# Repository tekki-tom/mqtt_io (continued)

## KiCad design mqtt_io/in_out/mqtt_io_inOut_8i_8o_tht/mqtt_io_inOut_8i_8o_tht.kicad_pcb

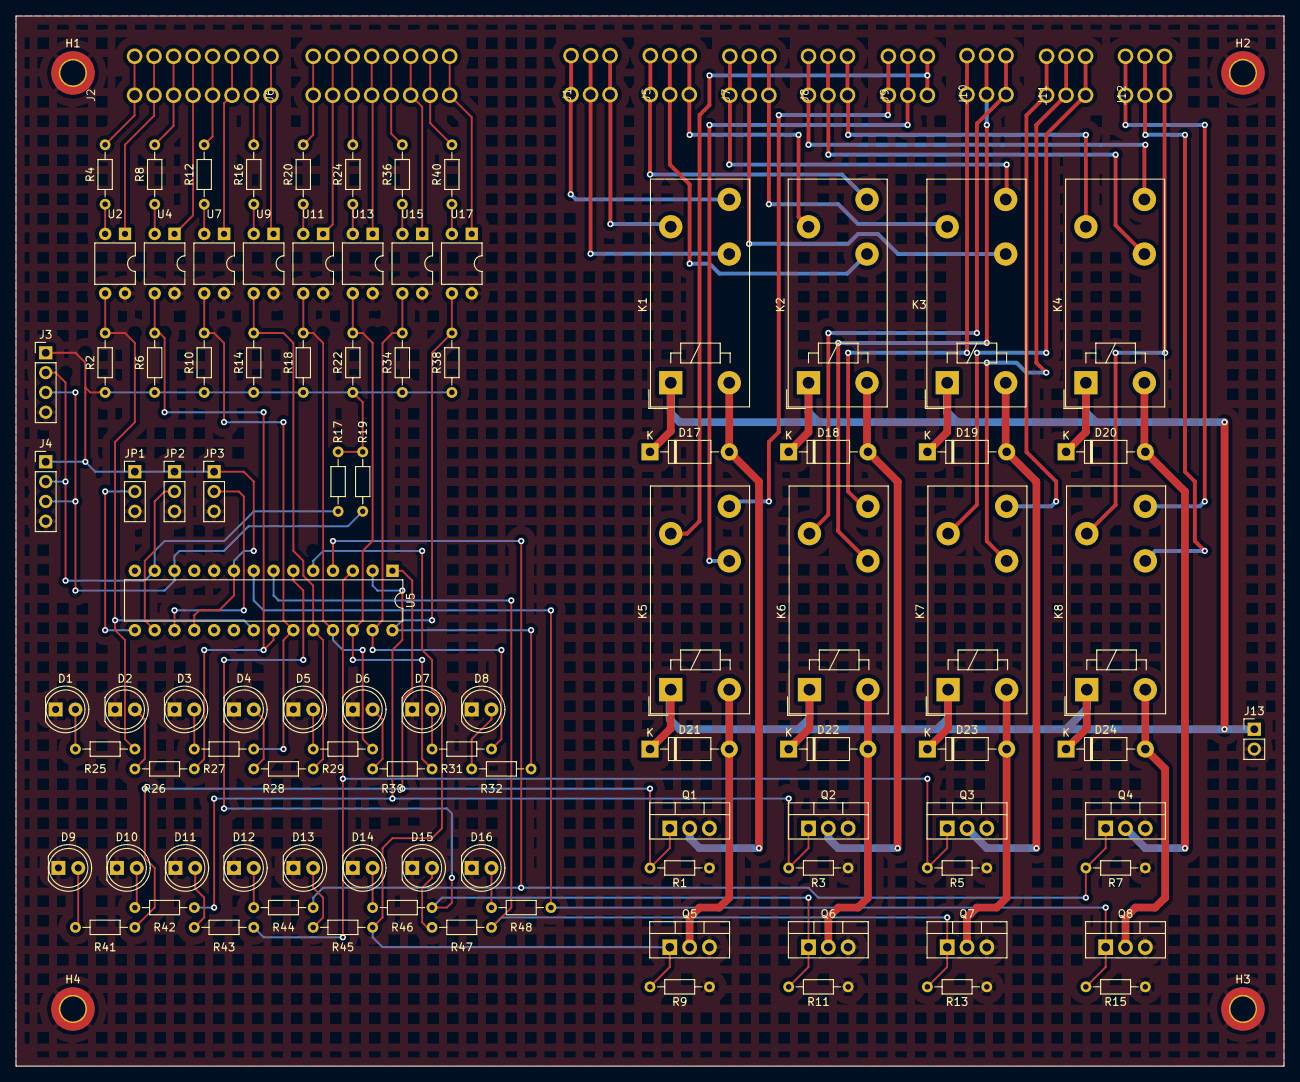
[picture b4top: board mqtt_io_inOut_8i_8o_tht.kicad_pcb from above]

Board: 2 copper layers, 162.6 x 134.6 mm, 111 parts (0 on the bottom side), 96 nets.

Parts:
D1, D2, D3, D4, D5, D6, D7, D8, D9, D10, D11, D12, D13, D14, D15, D16: LED; LED_D5.0mm
D17, D18, D19, D20, D21, D22, D23, D24: 1N4001; D_DO-41_SOD81_P10.16mm_Horizontal
H1, H2, H3, H4: MountingHole_Pad; MountingHole_3.2mm_M3_DIN965_Pad_TopBottom
J1, J5, J7, J8, J9, J10, J11, J12: AST_041-3
J2, J6: AST041-08
J3, J4: Conn_01x04_Pin; PinHeader_1x04_P2.54mm_Vertical
J13: Conn_01x02; PinHeader_1x02_P2.54mm_Vertical
JP1, JP2, JP3: Jumper_3_Open; PinHeader_1x03_P2.54mm_Vertical
K1, K2, K3, K4, K5, K6, K7, K8: FINDER-40.31; Relay_SPDT_Finder_40.31
Q1, Q2, Q3, Q4, Q5, Q6, Q7, Q8: IRFZ24N; TO-220-3_Vertical
R1, R3, R5, R7, R9, R11, R13, R15: 100kR; R_Axial_DIN0204_L3.6mm_D1.6mm_P7.62mm_Horizontal
R2, R6, R10, R14, R18, R22, R34, R38: 10kR; R_Axial_DIN0204_L3.6mm_D1.6mm_P7.62mm_Horizontal
R4, R8, R12, R16, R20, R24, R36, R40: 1200R; R_Axial_DIN0204_L3.6mm_D1.6mm_P7.62mm_Horizontal
R17, R19: 4k7; R_Axial_DIN0204_L3.6mm_D1.6mm_P7.62mm_Horizontal
R25, R26, R27, R28, R29, R30, R31, R32, R41, R42, R43, R44, R45, R46, R47, R48: 330R; R_Axial_DIN0204_L3.6mm_D1.6mm_P7.62mm_Horizontal
U2, U4, U7, U9, U11, U13, U15, U17: LTV-817; DIP-4_W7.62mm
U5: MCP23017_SP; DIP-28_W7.62mm

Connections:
/AD0: JP1.2 (C), U5.15 (A0)
/AD1: JP2.2 (C), U5.16 (A1)
/AD2: JP3.2 (C), U5.17 (A2)
/a0: R2.2, R25.2, U2.3, U5.21 (GPA0)
/a1: R6.2, R26.2, U4.3, U5.22 (GPA1)
/a2: R10.2, R27.2, U5.23 (GPA2), U7.3
/a3: R14.2, R28.2, U5.24 (GPA3), U9.3
/a4: R18.2, R29.2, U5.25 (GPA4), U11.3
/a5: R22.2, R30.2, U5.26 (GPA5), U13.3
/a6: R31.2, R34.2, U5.27 (GPA6), U15.3
/a7: R32.2, R38.2, U5.28 (GPA7), U17.3
/b0: Q1.1 (G), R1.2, R41.2, U5.1 (GPB0)
/b1: Q2.1 (G), R3.2, R42.2, U5.2 (GPB1)
/b2: Q3.1 (G), R5.2, R43.2, U5.3 (GPB2)
/b3: Q4.1 (G), R7.2, R44.2, U5.4 (GPB3)
/b4: Q5.1 (G), R9.2, R45.2, U5.5 (GPB4)
/b5: Q6.1 (G), R11.2, R46.2, U5.6 (GPB5)
/b6: Q7.1 (G), R13.2, R47.2, U5.7 (GPB6)
/b7: Q8.1 (G), R15.2, R48.2, U5.8 (GPB7)
GND: D1.1 (K), D2.1 (K), D3.1 (K), D4.1 (K), D5.1 (K), D6.1 (K), D7.1 (K), D8.1 (K), D9.1 (K), D10.1 (K), D11.1 (K), D12.1 (K), D13.1 (K), D14.1 (K), D15.1 (K), D16.1 (K), H1.1, H2.1, H3.1, H4.1, J3.4, J4.4, J13.2, JP1.3 (B), JP2.3 (B), JP3.3 (B), Q1.3 (S), Q2.3 (S), Q3.3 (S), Q4.3 (S), Q5.3 (S), Q6.3 (S), Q7.3 (S), Q8.3 (S), R1.1, R3.1, R5.1, R7.1, R9.1, R11.1, R13.1, R15.1, U2.4, U4.4, U5.10 (VSS), U7.4, U9.4, U11.4, U13.4, U15.4, U17.4
unnamed: D1.2 (A), R25.1
unnamed: D2.2 (A), R26.1
unnamed: D3.2 (A), R27.1
unnamed: D4.2 (A), R28.1
unnamed: D5.2 (A), R29.1
unnamed: D6.2 (A), R30.1
unnamed: D7.2 (A), R31.1
unnamed: D8.2 (A), R32.1
unnamed: D9.2 (A), R41.1
unnamed: D10.2 (A), R42.1
unnamed: D11.2 (A), R43.1
unnamed: D12.2 (A), R44.1
unnamed: D13.2 (A), R45.1
unnamed: D14.2 (A), R46.1
unnamed: D15.2 (A), R47.1
unnamed: D16.2 (A), R48.1
unnamed: D17.2 (A), K1.A2, Q1.2 (D)
unnamed: D18.2 (A), K2.A2, Q2.2 (D)
unnamed: D19.2 (A), K3.A2, Q3.2 (D)
unnamed: D20.2 (A), K4.A2, Q4.2 (D)
unnamed: D21.2 (A), K5.A2, Q5.2 (D)
unnamed: D22.2 (A), K6.A2, Q6.2 (D)
unnamed: D23.2 (A), K7.A2, Q7.2 (D)
unnamed: D24.2 (A), K8.A2, Q8.2 (D)
unnamed: J1.1, K1.14
unnamed: J1.2, K1.12
unnamed: J1.3, K1.11
unnamed: J2.1 (io), R4.2
unnamed: J2.2 (io), U2.1
unnamed: J2.3 (io), R8.2
unnamed: J2.4 (io), U4.1
unnamed: J2.5 (io), R12.2
unnamed: J2.6 (io), U7.1
unnamed: J2.7 (io), R16.2
unnamed: J2.8 (io), U9.1
unnamed: J3.2, J4.2, R17.1, U5.13 (SDA)
unnamed: J3.3, J4.3, R19.1, U5.12 (SCK)
unnamed: J5.1, K2.14
unnamed: J5.2, K2.12
unnamed: J5.3, K2.11
unnamed: J6.1 (io), R20.2
unnamed: J6.2 (io), U11.1
unnamed: J6.3 (io), R24.2
unnamed: J6.4 (io), U13.1
unnamed: J6.5 (io), R36.2
unnamed: J6.6 (io), U15.1
unnamed: J6.7 (io), R40.2
unnamed: J6.8 (io), U17.1
unnamed: J7.1, K3.14
unnamed: J7.2, K3.12
unnamed: J7.3, K3.11
unnamed: J8.1, K4.14
unnamed: J8.2, K4.12
unnamed: J8.3, K4.11
unnamed: J9.1, K5.14
unnamed: J9.2, K5.12
unnamed: J9.3, K5.11
unnamed: J10.1, K6.14
unnamed: J10.2, K6.12
unnamed: J10.3, K6.11
unnamed: J11.1, K7.14
unnamed: J11.2, K7.12
unnamed: J11.3, K7.11
unnamed: J12.1, K8.14
unnamed: J12.2, K8.12
unnamed: J12.3, K8.11
unnamed: R4.1, U2.2
unnamed: R8.1, U4.2
unnamed: R12.1, U7.2
unnamed: R16.1, U9.2
unnamed: R20.1, U11.2
unnamed: R24.1, U13.2
unnamed: R36.1, U15.2
unnamed: R40.1, U17.2
VCC: D17.1 (K), D18.1 (K), D19.1 (K), D20.1 (K), D21.1 (K), D22.1 (K), D23.1 (K), D24.1 (K), J13.1, K1.A1, K2.A1, K3.A1, K4.A1, K5.A1, K6.A1, K7.A1, K8.A1
VDD: J3.1, J4.1, JP1.1 (A), JP2.1 (A), JP3.1 (A), R2.1, R6.1, R10.1, R14.1, R17.2, R18.1, R19.2, R22.1, R34.1, R38.1, U5.9 (VDD), U5.18 (~RESET)

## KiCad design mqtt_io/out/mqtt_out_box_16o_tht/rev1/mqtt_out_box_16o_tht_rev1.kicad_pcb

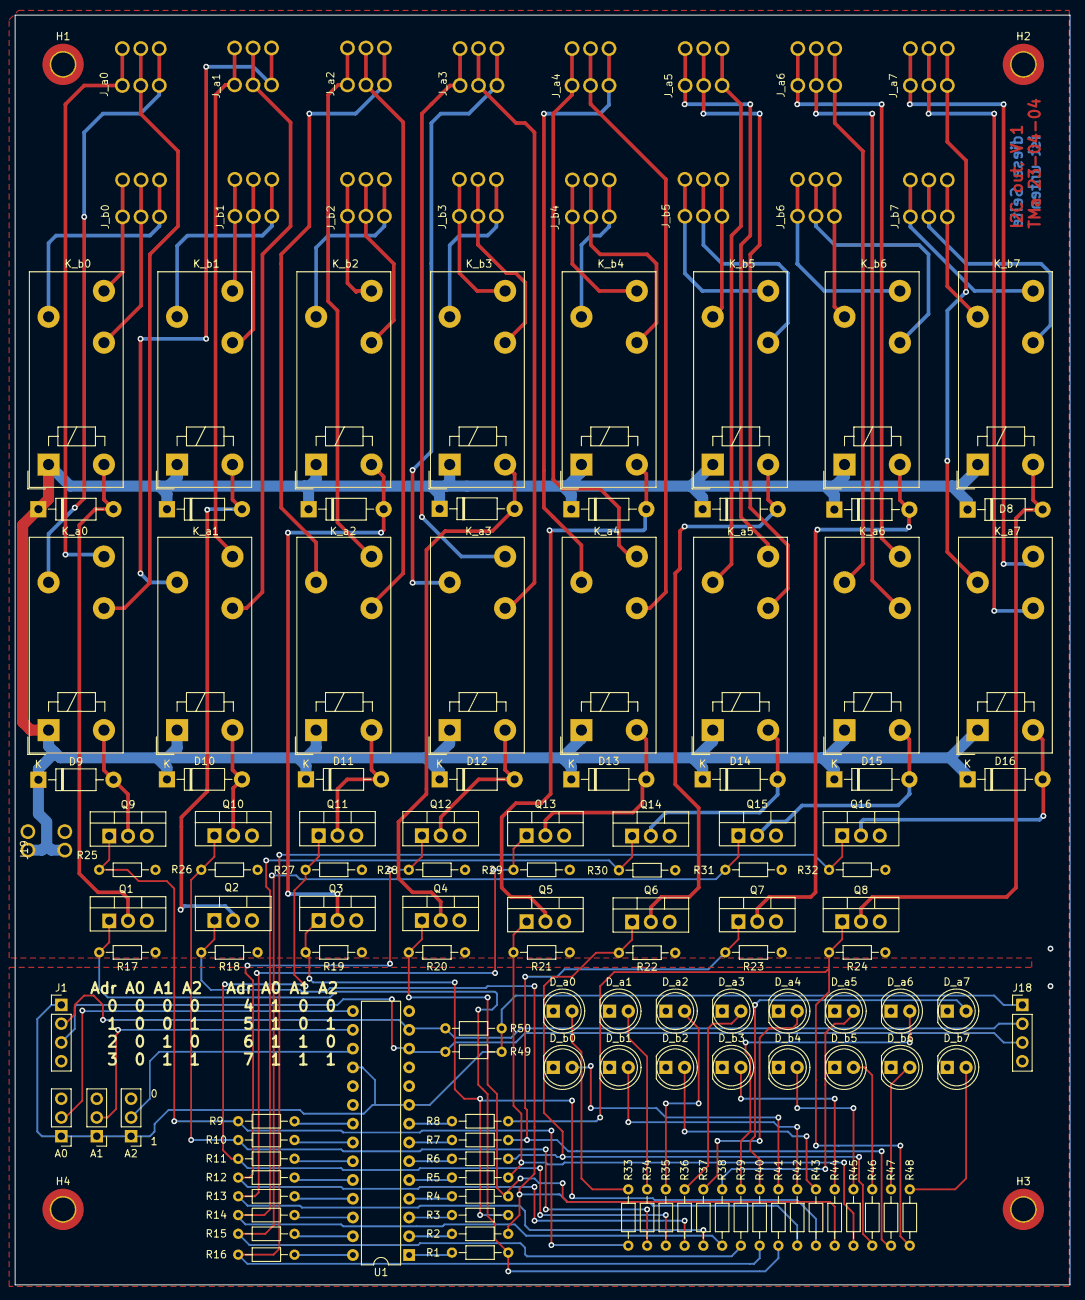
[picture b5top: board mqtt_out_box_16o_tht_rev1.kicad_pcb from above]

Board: 2 copper layers, 142.8 x 171.9 mm, 141 parts (0 on the bottom side), 120 nets.

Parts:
A0, A1, A2: Jumper_3_Open; PinHeader_1x03_P2.54mm_Vertical
D1, D2, D3, D4, D5, D6, D7, D8, D9, D10, D11, D12, D13, D14, D15, D16: 1N4001; D_DO-41_SOD81_P10.16mm_Horizontal
D_a0, D_a1, D_a2, D_a3, D_a4, D_a5, D_a6, D_a7: LED; LED_D5.0mm
D_b0, D_b1, D_b2, D_b3, D_b4, D_b5, D_b6, D_b7: LED; LED_D5.0mm
H1, H2, H3, H4: MountingHole_Pad; MountingHole_3.2mm_M3_DIN965_Pad_TopBottom
J1, J18: Conn_01x04_Pin; PinHeader_1x04_P2.54mm_Vertical
J19: AST_041-2
J_a0, J_a1, J_a2, J_a3, J_a4, J_a5, J_a6, J_a7: AST_041-3
J_b0, J_b1, J_b2, J_b3, J_b4, J_b5, J_b6, J_b7: AST_041-3
K_a0, K_a1, K_a2, K_a3, K_a4, K_a5, K_a6, K_a7: FINDER-40.31; Relay_SPDT_Finder_40.31
K_b0, K_b1, K_b2, K_b3, K_b4, K_b5, K_b6, K_b7: FINDER-40.31; Relay_SPDT_Finder_40.31
Q1, Q2, Q3, Q4, Q5, Q6, Q7, Q8, Q9, Q10, Q11, Q12, Q13, Q14, Q15, Q16: IRFZ24N; TO-220-3_Vertical
R1, R2, R3, R4, R5, R6, R7, R8, R9, R10, R11, R12, R13, R14, R15, R16: 100R; R_Axial_DIN0204_L3.6mm_D1.6mm_P7.62mm_Horizontal
R17, R18, R19, R20, R21, R22, R23, R24, R25, R26, R27, R28, R29, R30, R31, R32: 100kR; R_Axial_DIN0204_L3.6mm_D1.6mm_P7.62mm_Horizontal
R33, R34, R35, R36, R37, R38, R39, R40, R41, R42, R43, R44, R45, R46, R47, R48: 330R; R_Axial_DIN0204_L3.6mm_D1.6mm_P7.62mm_Horizontal
R49, R50: 4k7; R_Axial_DIN0204_L3.6mm_D1.6mm_P7.62mm_Horizontal
U1: MCP23017_SP; DIP-28_W7.62mm

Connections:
/AD0: A0.2 (C), U1.15 (A0)
/AD1: A1.2 (C), U1.16 (A1)
/AD2: A2.2 (C), U1.17 (A2)
/a0: Q9.1 (G), R9.2, R25.2, R33.2
/a1: Q10.1 (G), R10.2, R26.2, R34.2
/a2: Q11.1 (G), R11.2, R27.2, R35.2
/a3: Q12.1 (G), R12.2, R28.2, R36.2
/a4: Q13.1 (G), R13.2, R29.2, R37.2
/a5: Q14.1 (G), R14.2, R30.2, R38.2
/a6: Q15.1 (G), R15.2, R31.2, R39.2
/a7: Q16.1 (G), R16.2, R32.2, R40.2
/b0: Q1.1 (G), R1.2, R17.2, R41.2
/b1: Q2.1 (G), R2.2, R18.2, R42.2
/b2: Q3.1 (G), R3.2, R19.2, R43.2
/b3: Q4.1 (G), R4.2, R20.2, R44.2
/b4: Q5.1 (G), R5.2, R21.2, R45.2
/b5: Q6.1 (G), R6.2, R22.2, R46.2
/b6: Q7.1 (G), R7.2, R23.2, R47.2
/b7: Q8.1 (G), R8.2, R24.2, R48.2
GND: A0.3 (B), A1.3 (B), A2.3 (B), D_a0.1 (K), D_a1.1 (K), D_a2.1 (K), D_a3.1 (K), D_a4.1 (K), D_a5.1 (K), D_a6.1 (K), D_a7.1 (K), D_b0.1 (K), D_b1.1 (K), D_b2.1 (K), D_b3.1 (K), D_b4.1 (K), D_b5.1 (K), D_b6.1 (K), D_b7.1 (K), H1.1, H2.1, H3.1, H4.1, J1.4, J18.4, J19.2, Q1.3 (S), Q2.3 (S), Q3.3 (S), Q4.3 (S), Q5.3 (S), Q6.3 (S), Q7.3 (S), Q8.3 (S), Q9.3 (S), Q10.3 (S), Q11.3 (S), Q12.3 (S), Q13.3 (S), Q14.3 (S), Q15.3 (S), Q16.3 (S), R17.1, R18.1, R19.1, R20.1, R21.1, R22.1, R23.1, R24.1, R25.1, R26.1, R27.1, R28.1, R29.1, R30.1, R31.1, R32.1, U1.10 (VSS)
unnamed: D1.2 (A), K_b0.A2, Q1.2 (D)
unnamed: D2.2 (A), K_b1.A2, Q2.2 (D)
unnamed: D3.2 (A), K_b2.A2, Q3.2 (D)
unnamed: D4.2 (A), K_b3.A2, Q4.2 (D)
unnamed: D5.2 (A), K_b4.A2, Q5.2 (D)
unnamed: D6.2 (A), K_b5.A2, Q6.2 (D)
unnamed: D7.2 (A), K_b6.A2, Q7.2 (D)
unnamed: D8.2 (A), K_b7.A2, Q8.2 (D)
unnamed: D9.2 (A), K_a0.A2, Q9.2 (D)
unnamed: D10.2 (A), K_a1.A2, Q10.2 (D)
unnamed: D11.2 (A), K_a2.A2, Q11.2 (D)
unnamed: D12.2 (A), K_a3.A2, Q12.2 (D)
unnamed: D13.2 (A), K_a4.A2, Q13.2 (D)
unnamed: D14.2 (A), K_a5.A2, Q14.2 (D)
unnamed: D15.2 (A), K_a6.A2, Q15.2 (D)
unnamed: D16.2 (A), K_a7.A2, Q16.2 (D)
unnamed: D_a0.2 (A), R33.1
unnamed: D_a1.2 (A), R34.1
unnamed: D_a2.2 (A), R35.1
unnamed: D_a3.2 (A), R36.1
unnamed: D_a4.2 (A), R37.1
unnamed: D_a5.2 (A), R38.1
unnamed: D_a6.2 (A), R39.1
unnamed: D_a7.2 (A), R40.1
unnamed: D_b0.2 (A), R41.1
unnamed: D_b1.2 (A), R42.1
unnamed: D_b2.2 (A), R43.1
unnamed: D_b3.2 (A), R44.1
unnamed: D_b4.2 (A), R45.1
unnamed: D_b5.2 (A), R46.1
unnamed: D_b6.2 (A), R47.1
unnamed: D_b7.2 (A), R48.1
unnamed: J1.2, J18.2, R50.1, U1.13 (SDA)
unnamed: J1.3, J18.3, R49.1, U1.12 (SCK)
unnamed: J_a0.1, K_a0.14
unnamed: J_a0.2, K_a0.12
unnamed: J_a0.3, K_a0.11
unnamed: J_a1.1, K_a1.14
unnamed: J_a1.2, K_a1.12
unnamed: J_a1.3, K_a1.11
unnamed: J_a2.1, K_a2.14
unnamed: J_a2.2, K_a2.12
unnamed: J_a2.3, K_a2.11
unnamed: J_a3.1, K_a3.14
unnamed: J_a3.2, K_a3.12
unnamed: J_a3.3, K_a3.11
unnamed: J_a4.1, K_a4.14
unnamed: J_a4.2, K_a4.12
unnamed: J_a4.3, K_a4.11
unnamed: J_a5.1, K_a5.14
unnamed: J_a5.2, K_a5.12
unnamed: J_a5.3, K_a5.11
unnamed: J_a6.1, K_a6.14
unnamed: J_a6.2, K_a6.12
unnamed: J_a6.3, K_a6.11
unnamed: J_a7.1, K_a7.14
unnamed: J_a7.2, K_a7.12
unnamed: J_a7.3, K_a7.11
unnamed: J_b0.1, K_b0.14
unnamed: J_b0.2, K_b0.12
unnamed: J_b0.3, K_b0.11
unnamed: J_b1.1, K_b1.14
unnamed: J_b1.2, K_b1.12
unnamed: J_b1.3, K_b1.11
unnamed: J_b2.1, K_b2.14
unnamed: J_b2.2, K_b2.12
unnamed: J_b2.3, K_b2.11
unnamed: J_b3.1, K_b3.14
unnamed: J_b3.2, K_b3.12
unnamed: J_b3.3, K_b3.11
unnamed: J_b4.1, K_b4.14
unnamed: J_b4.2, K_b4.12
unnamed: J_b4.3, K_b4.11
unnamed: J_b5.1, K_b5.14
unnamed: J_b5.2, K_b5.12
unnamed: J_b5.3, K_b5.11
unnamed: J_b6.1, K_b6.14
unnamed: J_b6.2, K_b6.12
unnamed: J_b6.3, K_b6.11
unnamed: J_b7.1, K_b7.14
unnamed: J_b7.2, K_b7.12
unnamed: J_b7.3, K_b7.11
unnamed: R9.1, U1.21 (GPA0)
unnamed: R10.1, U1.22 (GPA1)
unnamed: R11.1, U1.23 (GPA2)
unnamed: R12.1, U1.24 (GPA3)
unnamed: R13.1, U1.25 (GPA4)
unnamed: R14.1, U1.26 (GPA5)
unnamed: R15.1, U1.27 (GPA6)
unnamed: R16.1, U1.28 (GPA7)
unnamed: R1.1, U1.1 (GPB0)
unnamed: R2.1, U1.2 (GPB1)
unnamed: R3.1, U1.3 (GPB2)
unnamed: R4.1, U1.4 (GPB3)
unnamed: R5.1, U1.5 (GPB4)
unnamed: R6.1, U1.6 (GPB5)
unnamed: R7.1, U1.7 (GPB6)
unnamed: R8.1, U1.8 (GPB7)
VCC: D1.1 (K), D2.1 (K), D3.1 (K), D4.1 (K), D5.1 (K), D6.1 (K), D7.1 (K), D8.1 (K), D9.1 (K), D10.1 (K), D11.1 (K), D12.1 (K), D13.1 (K), D14.1 (K), D15.1 (K), D16.1 (K), J19.1, K_a0.A1, K_a1.A1, K_a2.A1, K_a3.A1, K_a4.A1, K_a5.A1, K_a6.A1, K_a7.A1, K_b0.A1, K_b1.A1, K_b2.A1, K_b3.A1, K_b4.A1, K_b5.A1, K_b6.A1, K_b7.A1
VDD: A0.1 (A), A1.1 (A), A2.1 (A), J1.1, J18.1, R49.2, R50.2, U1.9 (VDD), U1.18 (~RESET)

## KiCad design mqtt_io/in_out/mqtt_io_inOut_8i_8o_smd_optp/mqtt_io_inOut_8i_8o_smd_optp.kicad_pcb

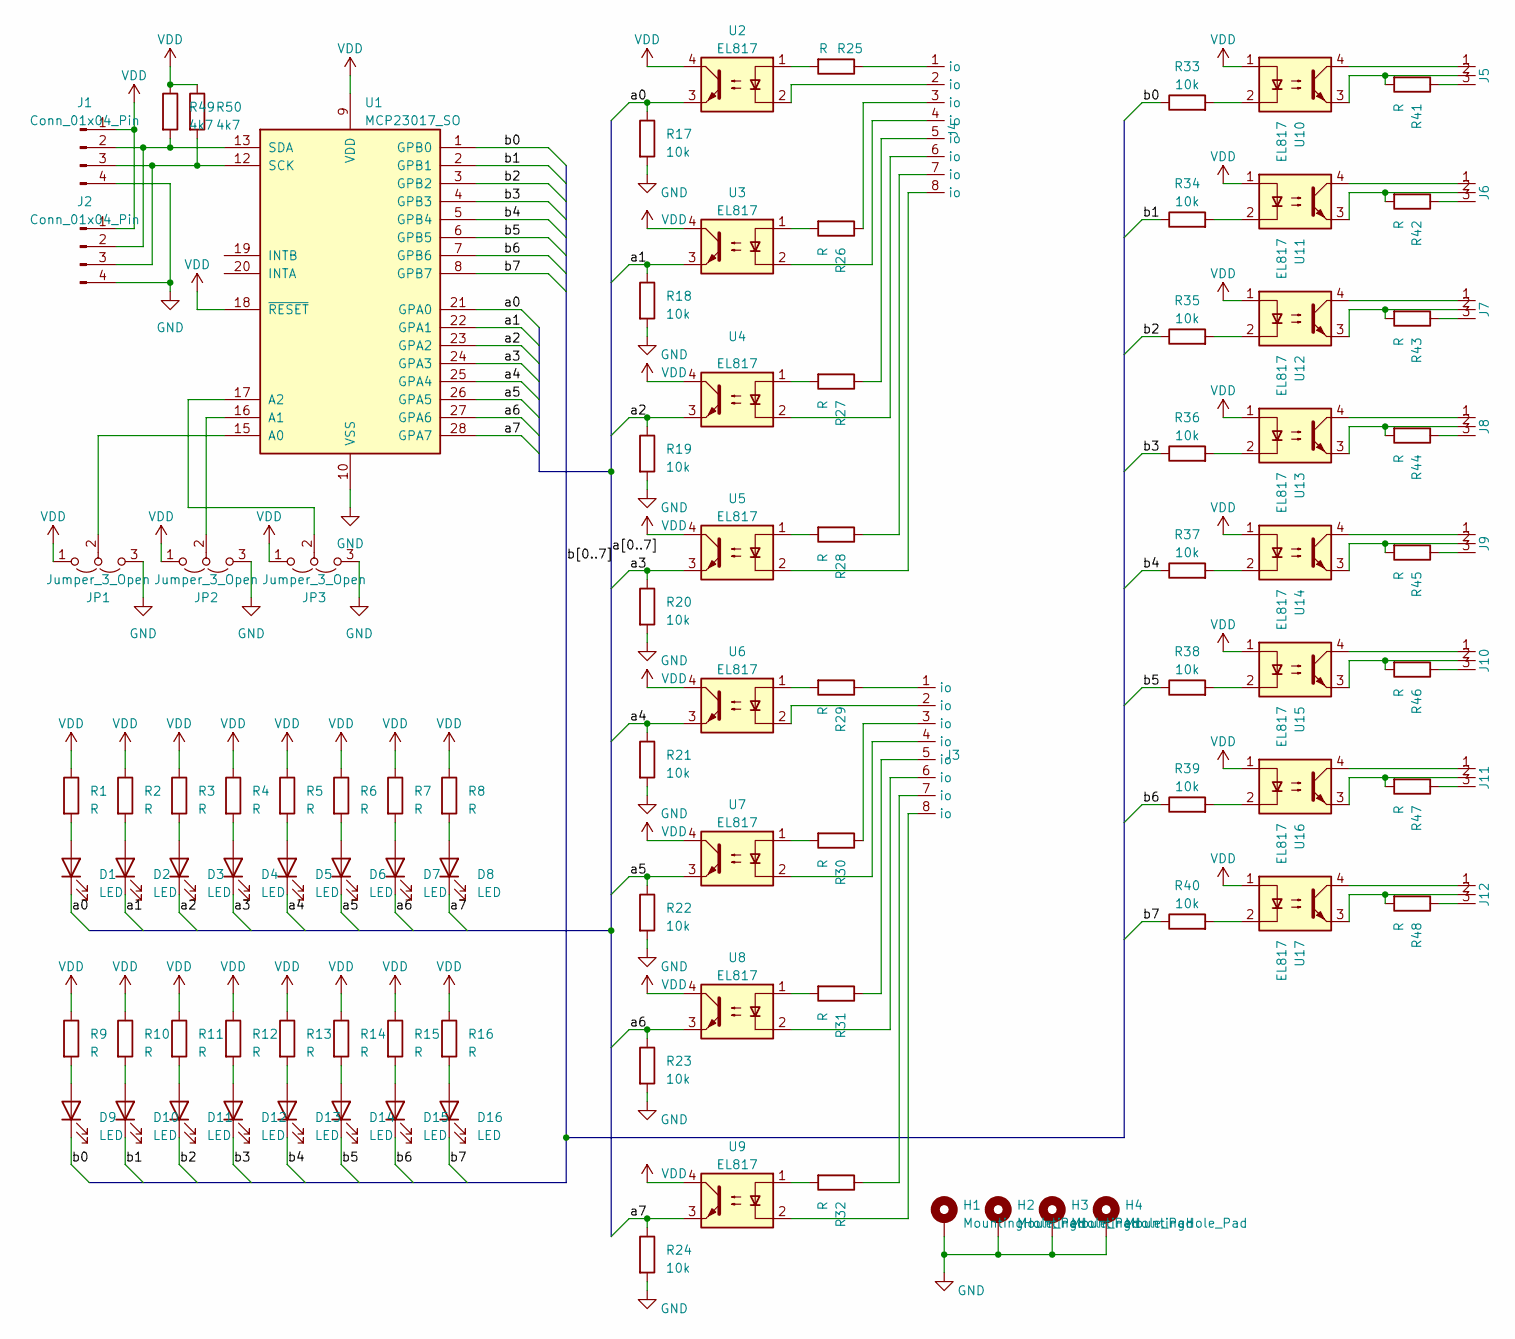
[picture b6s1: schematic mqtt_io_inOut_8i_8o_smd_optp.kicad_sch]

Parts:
D1, D2, D3, D4, D5, D6, D7, D8, D9, D10, D11, D12, D13, D14, D15, D16: LED; LED_1206_3216Metric_Pad1.42x1.75mm_HandSolder
H1, H2, H3, H4: MountingHole_Pad; MountingHole_3.2mm_M3_DIN965_Pad_TopBottom
J1, J2: Conn_01x04_Pin; PinHeader_1x04_P2.54mm_Vertical
J3, J4: AST041-08
J5, J6, J7, J8, J9, J10, J11, J12: AST_041-3
JP1, JP2, JP3: Jumper_3_Open; PinHeader_1x03_P2.54mm_Vertical
R1, R2, R3, R4, R5, R6, R7, R8, R9, R10, R11, R12, R13, R14, R15, R16, R25, R26, R27, R28, R29, R30, R31, R32, R41, R42, R43, R44, R45, R46, R47, R48: R; R_1206_3216Metric_Pad1.30x1.75mm_HandSolder
R17, R18, R19, R20, R21, R22, R23, R24, R33, R34, R35, R36, R37, R38, R39, R40: 10k; R_1206_3216Metric_Pad1.30x1.75mm_HandSolder
R49, R50: 4k7; R_1206_3216Metric_Pad1.30x1.75mm_HandSolder
U1: MCP23017_SO; SOIC-28W_7.5x17.9mm_P1.27mm
U2, U3, U4, U5, U6, U7, U8, U9, U10, U11, U12, U13, U14, U15, U16, U17: EL817; DIP-4_W7.62mm_SMDSocket_SmallPads

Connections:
/a0: D1.1 (K), R17.1, U1.21 (GPA0), U2.3
/a1: D2.1 (K), R18.1, U1.22 (GPA1), U3.3
/a2: D3.1 (K), R19.1, U1.23 (GPA2), U4.3
/a3: D4.1 (K), R20.1, U1.24 (GPA3), U5.3
/a4: D5.1 (K), R21.1, U1.25 (GPA4), U6.3
/a5: D6.1 (K), R22.1, U1.26 (GPA5), U7.3
/a6: D7.1 (K), R23.1, U1.27 (GPA6), U8.3
/a7: D8.1 (K), R24.1, U1.28 (GPA7), U9.3
/b0: D9.1 (K), R33.1, U1.1 (GPB0)
/b1: D10.1 (K), R34.1, U1.2 (GPB1)
/b2: D11.1 (K), R35.1, U1.3 (GPB2)
/b3: D12.1 (K), R36.1, U1.4 (GPB3)
/b4: D13.1 (K), R37.1, U1.5 (GPB4)
/b5: D14.1 (K), R38.1, U1.6 (GPB5)
/b6: D15.1 (K), R39.1, U1.7 (GPB6)
/b7: D16.1 (K), R40.1, U1.8 (GPB7)
GND: H1.1, H2.1, H3.1, H4.1, J1.4, J2.4, JP1.3 (B), JP2.3 (B), JP3.3 (B), R17.2, R18.2, R19.2, R20.2, R21.2, R22.2, R23.2, R24.2, U1.10 (VSS)
unnamed: D1.2 (A), R1.2
unnamed: D2.2 (A), R2.2
unnamed: D3.2 (A), R3.2
unnamed: D4.2 (A), R4.2
unnamed: D5.2 (A), R5.2
unnamed: D6.2 (A), R6.2
unnamed: D7.2 (A), R7.2
unnamed: D8.2 (A), R8.2
unnamed: D9.2 (A), R9.2
unnamed: D10.2 (A), R10.2
unnamed: D11.2 (A), R11.2
unnamed: D12.2 (A), R12.2
unnamed: D13.2 (A), R13.2
unnamed: D14.2 (A), R14.2
unnamed: D15.2 (A), R15.2
unnamed: D16.2 (A), R16.2
unnamed: J1.2, J2.2, R49.2, U1.13 (SDA)
unnamed: J1.3, J2.3, R50.2, U1.12 (SCK)
unnamed: J3.1 (io), R29.1
unnamed: J3.2 (io), U6.2
unnamed: J3.3 (io), R30.1
unnamed: J3.4 (io), U7.2
unnamed: J3.5 (io), R31.1
unnamed: J3.6 (io), U8.2
unnamed: J3.7 (io), R32.1
unnamed: J3.8 (io), U9.2
unnamed: J4.1 (io), R25.1
unnamed: J4.2 (io), U2.2
unnamed: J4.3 (io), R26.1
unnamed: J4.4 (io), U3.2
unnamed: J4.5 (io), R27.1
unnamed: J4.6 (io), U4.2
unnamed: J4.7 (io), R28.1
unnamed: J4.8 (io), U5.2
unnamed: J5.1, U10.4
unnamed: J5.2, R41.2, U10.3
unnamed: J5.3, R41.1
unnamed: J6.1, U11.4
unnamed: J6.2, R42.2, U11.3
unnamed: J6.3, R42.1
unnamed: J7.1, U12.4
unnamed: J7.2, R43.2, U12.3
unnamed: J7.3, R43.1
unnamed: J8.1, U13.4
unnamed: J8.2, R44.2, U13.3
unnamed: J8.3, R44.1
unnamed: J9.1, U14.4
unnamed: J9.2, R45.2, U14.3
unnamed: J9.3, R45.1
unnamed: J10.1, U15.4
unnamed: J10.2, R46.2, U15.3
unnamed: J10.3, R46.1
unnamed: J11.1, U16.4
unnamed: J11.2, R47.2, U16.3
unnamed: J11.3, R47.1
unnamed: J12.1, U17.4
unnamed: J12.2, R48.2, U17.3
unnamed: J12.3, R48.1
unnamed: JP1.2 (C), U1.15 (A0)
unnamed: JP2.2 (C), U1.16 (A1)
unnamed: JP3.2 (C), U1.17 (A2)
unnamed: R25.2, U2.1
unnamed: R26.2, U3.1
unnamed: R27.2, U4.1
unnamed: R28.2, U5.1
unnamed: R29.2, U6.1
unnamed: R30.2, U7.1
unnamed: R31.2, U8.1
unnamed: R32.2, U9.1
unnamed: R33.2, U10.2
unnamed: R34.2, U11.2
unnamed: R35.2, U12.2
unnamed: R36.2, U13.2
unnamed: R37.2, U14.2
unnamed: R38.2, U15.2
unnamed: R39.2, U16.2
unnamed: R40.2, U17.2
VDD: J1.1, J2.1, JP1.1 (A), JP2.1 (A), JP3.1 (A), R1.1, R2.1, R3.1, R4.1, R5.1, R6.1, R7.1, R8.1, R9.1, R10.1, R11.1, R12.1, R13.1, R14.1, R15.1, R16.1, R49.1, R50.1, U1.9 (VDD), U1.18 (~RESET), U2.4, U3.4, U4.4, U5.4, U6.4, U7.4, U8.4, U9.4, U10.1, U11.1, U12.1, U13.1, U14.1, U15.1, U16.1, U17.1

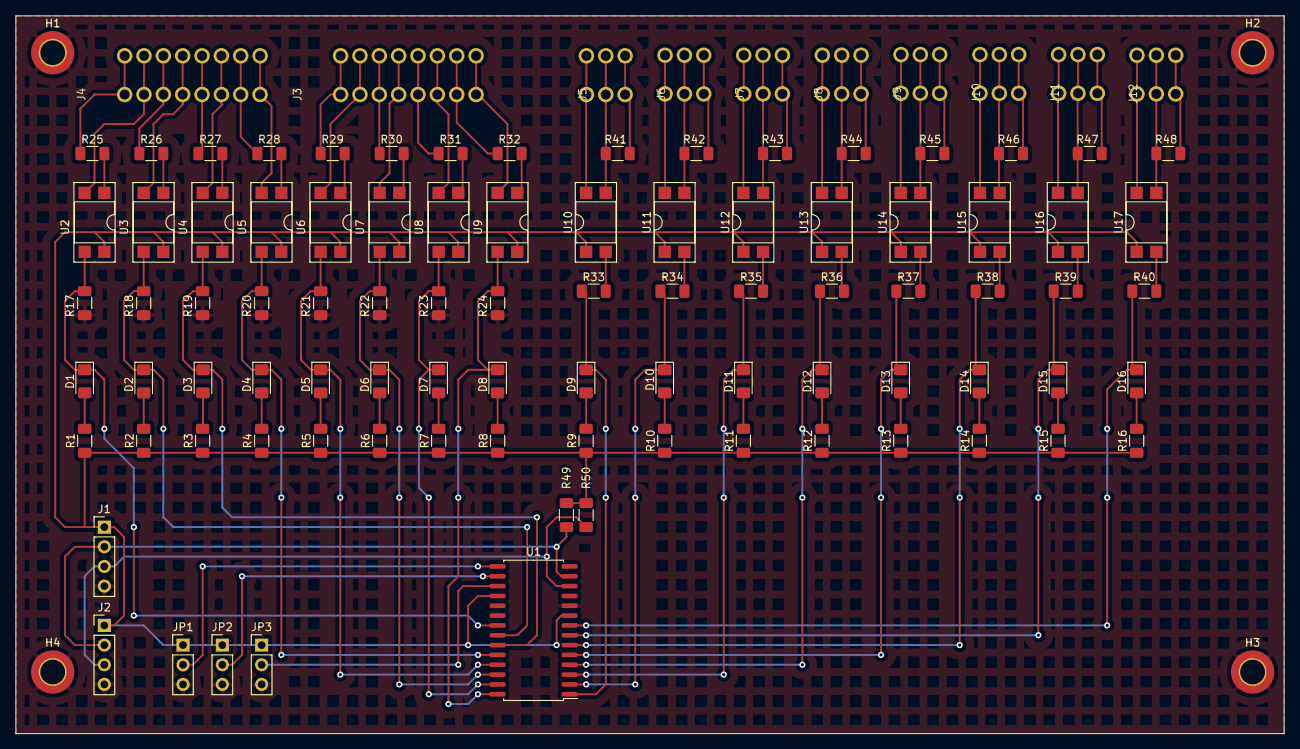
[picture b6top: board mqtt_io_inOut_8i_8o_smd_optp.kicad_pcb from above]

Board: 2 copper layers, 163.8 x 92.7 mm, 102 parts (0 on the bottom side), 95 nets.

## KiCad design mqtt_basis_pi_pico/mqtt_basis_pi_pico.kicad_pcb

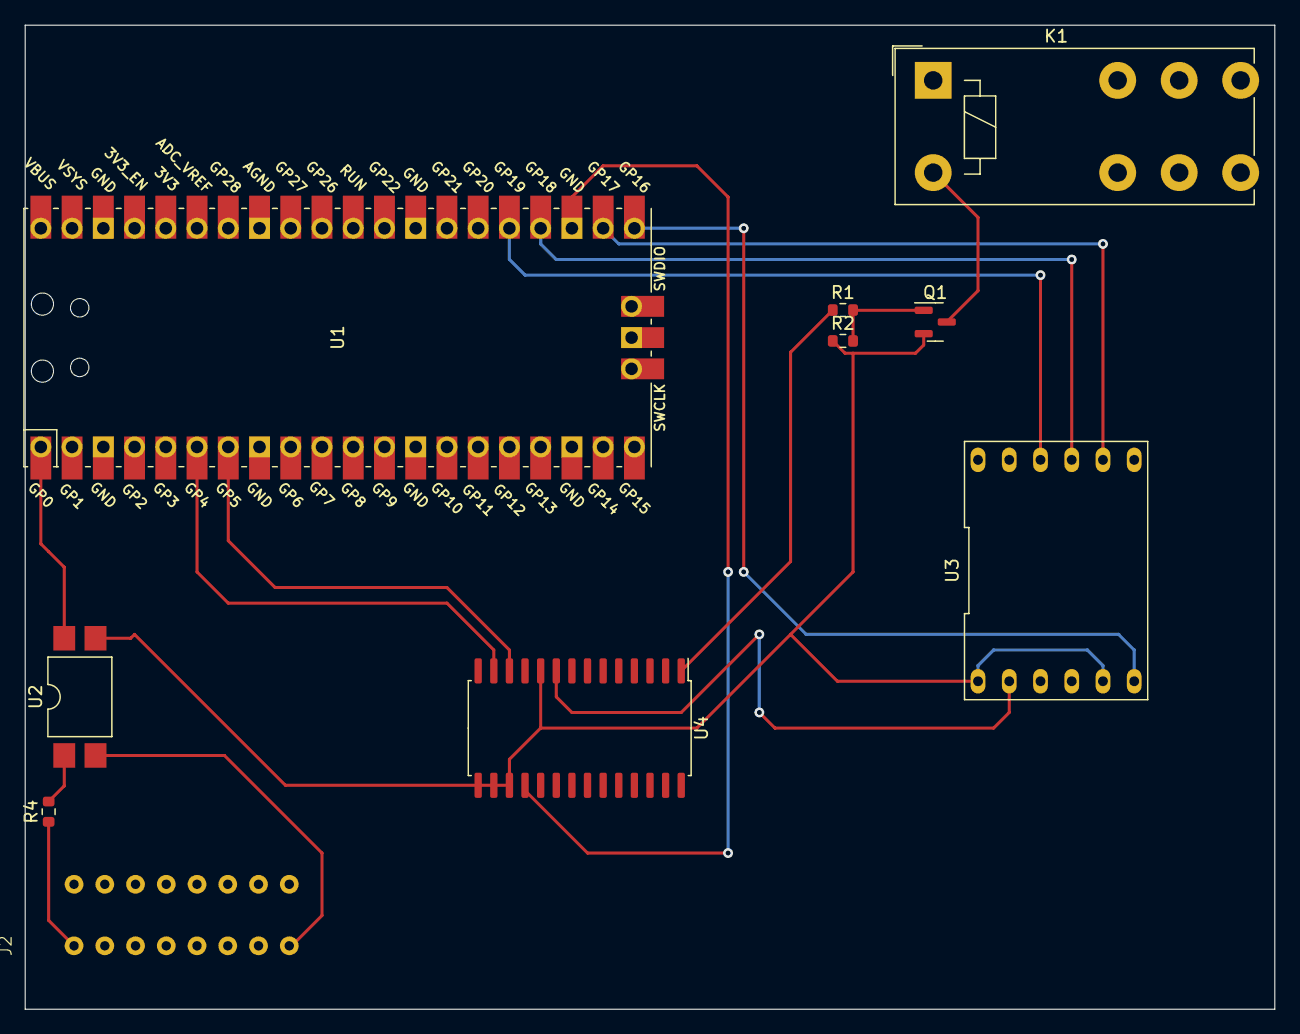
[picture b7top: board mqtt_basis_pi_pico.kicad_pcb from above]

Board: 2 copper layers, 101.6 x 80.0 mm, 10 parts (0 on the bottom side), 16 nets.

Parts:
J2: AST041-08
K1: FINDER-40.52; Relay_DPDT_Finder_40.52
Q1: IRLML0030; SOT-23
R1: 100; R_0603_1608Metric
R2: 100k; R_0603_1608Metric
R4: R; R_0603_1608Metric
U1: Pico; RPi_Pico_SMD_TH
U2: LTV-817S; SMDIP-4_W9.53mm
U3: w5500_spi_modul
U4: MCP23017_SO; SOIC-28W_7.5x17.9mm_P1.27mm

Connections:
GND: Q1.2 (S), R2.1, U1.42 (GND), U2.3, U3.1 (GND), U3.5 (RST), U4.10 (VSS), U4.15 (A0), U4.16 (A1), U4.17 (A2)
unnamed: J2.1 (io), R4.1
unnamed: J2.8 (io), U2.2
unnamed: K1.A2, Q1.3 (D)
unnamed: Q1.1 (G), R1.2, R2.2
unnamed: R4.2, U2.1
unnamed: U1.1 (GPIO0), U2.4
unnamed: U1.6 (GPIO4), U4.13 (SDA)
unnamed: U1.7 (GPIO5), U4.12 (SCK)
unnamed: U1.21 (GPIO16), U3.6 (MI)
unnamed: U1.22 (GPIO17), U3.8 (CS)
unnamed: U1.24 (GPIO18), U3.9 (SCK)
unnamed: U1.25 (GPIO19), U3.10 (MO)
unnamed: R1.1, U4.1 (GPB0)
unnamed: U1.23 (GND), U4.18 (~RESET)
VCC: K1.A1, U3.2 (VCC), U4.9 (VDD)

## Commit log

2023-03-09 erster checkin
2023-03-11 platine_out_23017 (i2c), smd v0.1
2023-03-19 repos aufgeräumt und Dateien verschoben
2023-04-01 Pullup für ic2 eingefügt (4k7)
2023-04-01 Beispiel-Code für ATMega328p / (Arduino Uno) eingefügt
2023-04-23 neue Dateien eingefügt.
    out Platine rev 2, testprogramm für pi pico
2023-06-25 Kleine Korrekturen
2023-06-25 umbau auf smd
2023-06-29 FET durch anderes Modell ersetzt
    neu: 2N7000
2023-06-30 Platine geändert, BSS138
    BSS138 SMD statt 2n7000 THT
2023-06-30 kleine Anpassungen
2023-07-16 Wert von R33 korrigiert
2023-07-16 neue Tests für i2c Expander
    "Lauflicht" Test
    io_expander Nr beachten!
2023-09-09 Jumper, Beschriftung
    Jumper für pullupWiderstände bei SDA und SCK eingefügt. Die Widerstände
    sind nun zuschaltbar.
    Beschriftung für in SDA/SCK/GND und Spannungsversorgung angebracht.
    PDFs neu generiert.
2023-09-10 Nachtrag für todo-Liste
2024-04-09 Neue Version angelegt (SMD, Opto THT)
